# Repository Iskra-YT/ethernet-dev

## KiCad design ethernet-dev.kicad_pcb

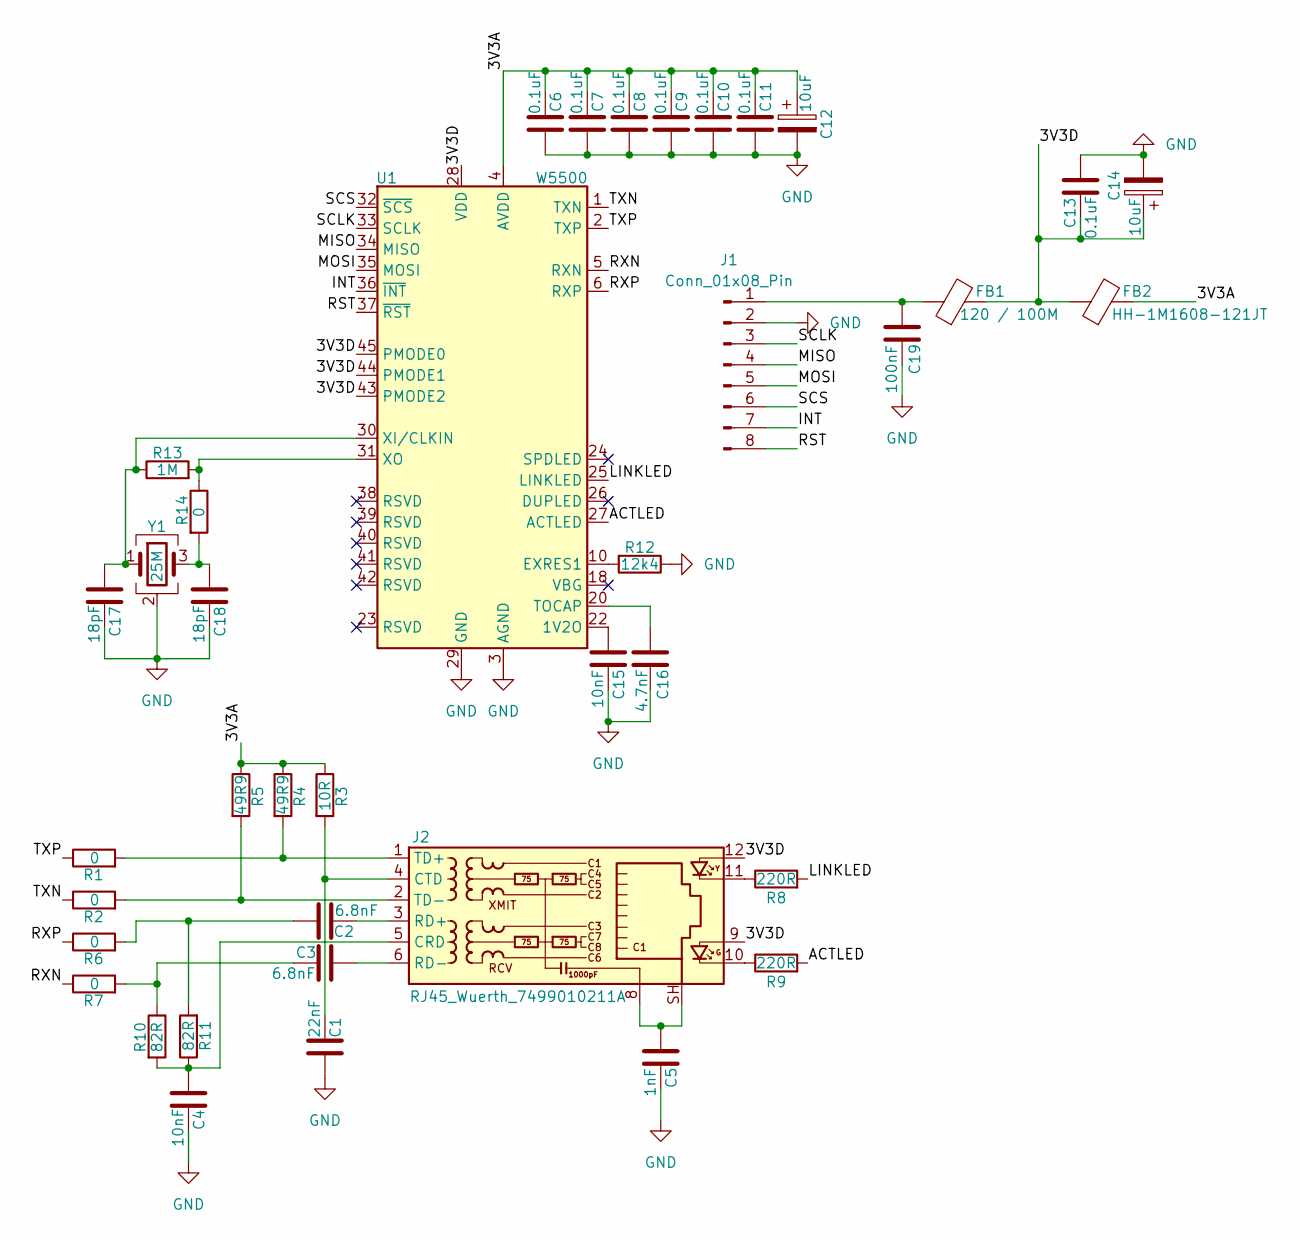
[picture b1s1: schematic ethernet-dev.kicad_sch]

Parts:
C1: 22nF; C_0805_2012Metric
C2, C3: 6.8nF; C_0805_2012Metric
C4, C15: 10nF; C_0805_2012Metric
C5: 1nF; C_0805_2012Metric
C6, C7, C8, C9, C10, C11, C13: 0.1uF; C_0805_2012Metric
C12, C14: 10uF; C_0805_2012Metric
C16: 4.7nF; C_0805_2012Metric
C17, C18: 18pF; C_0805_2012Metric
C19: 100nF; C_0805_2012Metric
FB1: 120 / 100M; L_0603_1608Metric
FB2: HH-1M1608-121JT; R_0603_1608Metric
J1: Conn_01x08_Pin; PinHeader_1x08_P2.54mm_Vertical
J2: RJ45_Wuerth_7499010211A; RJ45_Wuerth_7499010211A_Horizontal
R1, R2, R6, R7, R14: 0; R_0805_2012Metric
R3: 10R; R_0805_2012Metric
R4, R5: 49R9; R_0805_2012Metric
R8, R9: 220R; R_0805_2012Metric
R10, R11: 82R; R_0805_2012Metric
R12: 12k4; R_0805_2012Metric
R13: 1M; R_0805_2012Metric
U1: W5500; LQFP-48_7x7mm_P0.5mm
Y1: 25M; Crystal_SMD_3225-4Pin_3.2x2.5mm

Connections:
/3V3A: C6.1, C7.1, C8.1, C9.1, C10.1, C11.1, C12.1, FB2.2, R3.1, R4.1, R5.1, U1.4 (AVDD), U1.8 (AVDD), U1.11 (AVDD), U1.15 (AVDD), U1.17 (AVDD), U1.21 (AVDD)
/3V3D: C13.1, C14.1, FB1.2, FB2.1, J2.9, J2.12, U1.28 (VDD), U1.43 (PMODE2), U1.44 (PMODE1), U1.45 (PMODE0)
/ACTLED: R9.2, U1.27 (ACTLED)
/INT: J1.7, U1.36 (~INT)
/LINKLED: R8.2, U1.25 (LINKLED)
/MISO: J1.4, U1.34 (MISO)
/MOSI: J1.5, U1.35 (MOSI)
/RST: J1.8, U1.37 (~RST)
/RXN: R7.1, U1.5 (RXN)
/RXP: R6.1, U1.6 (RXP)
/SCLK: J1.3, U1.33 (SCLK)
/SCS: J1.6, U1.32 (~SCS)
/TXN: R2.1, U1.1 (TXN)
/TXP: R1.1, U1.2 (TXP)
GND: C1.2, C4.2, C5.2, C6.2, C7.2, C8.2, C9.2, C10.2, C11.2, C12.2, C13.2, C14.2, C15.2, C16.2, C17.2, C18.2, C19.2, J1.2, R12.1, U1.3 (AGND), U1.9 (AGND), U1.14 (AGND), U1.16 (AGND), U1.19 (AGND), U1.29 (GND), U1.48 (AGND), Y1.2 (G), Y1.4 (G)
unnamed: C2.2, R6.2, R11.2
unnamed: C3.1, R7.2, R10.1
unnamed: C5.1, J2.8, J2.SH
unnamed: C18.1, R14.2, Y1.3
unnamed: C19.1, FB1.1, J1.1
unnamed: C4.1, J2.5 (CRD), R10.2, R11.1
unnamed: C1.1, J2.4 (CTD), R3.2
unnamed: J2.10, R9.1
unnamed: J2.11, R8.1
unnamed: C2.1, J2.3 (RD+)
unnamed: C3.2, J2.6 (RD-)
unnamed: J2.1 (TD+), R1.2, R4.2
unnamed: J2.2 (TD-), R2.2, R5.2
unnamed: C15.1, U1.22 (1V2O)
unnamed: R12.2, U1.10 (EXRES1)
unnamed: C16.1, U1.20 (TOCAP)
unnamed: C17.1, R13.1, U1.30 (XI/CLKIN), Y1.1
unnamed: R13.2, R14.1, U1.31 (XO)

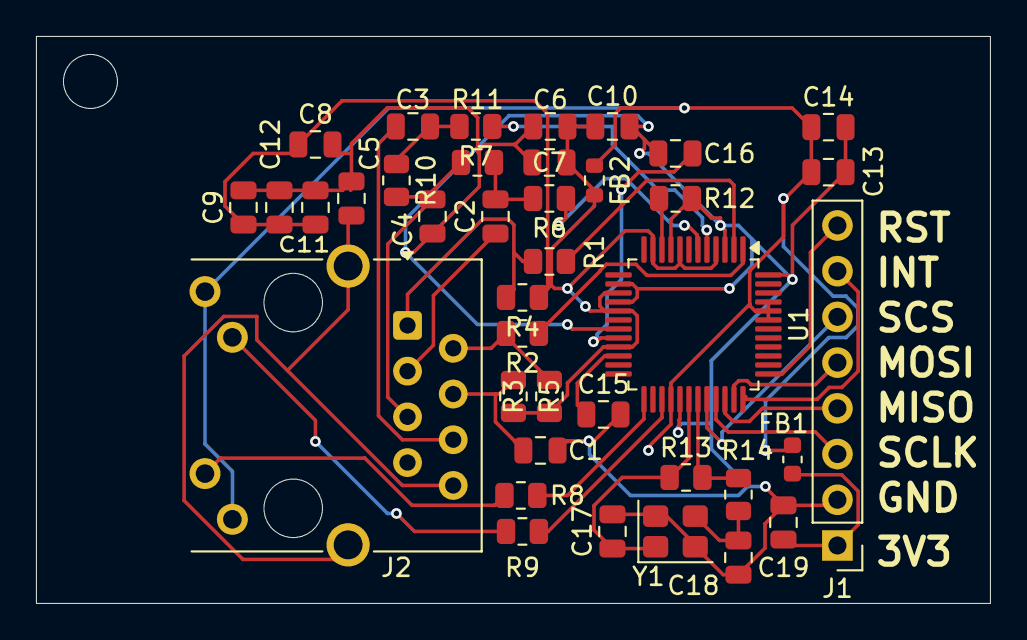
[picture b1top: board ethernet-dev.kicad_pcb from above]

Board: 2 copper layers, 53.0 x 31.5 mm, 39 parts (0 on the bottom side), 33 nets.
